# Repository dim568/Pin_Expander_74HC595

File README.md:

# Pin_Expander_74HC595
SPI Expander Board On 74HC595

KiCAD 4.0.4
PCB Design 03.05.17

PCB Have SilkScreen numeration error
- 23 -> 16
- 22 -> 17
- 21 -> 18
- 20 -> 19
- 19 -> 20
- 18 -> 21
- 17 -> 22
- 16 -> 23
- 15 -> 08
- 14 -> 09
- 13 -> 10
- 12 -> 11
- 11 -> 12
- 10 -> 13
- 09 -> 14
- 08 -> 15
- 07 -> 00
- 06 -> 01
- 05 -> 02
- 04 -> 03
- 03 -> 04
- 02 -> 05
- 01 -> 06
- 00 -> 07

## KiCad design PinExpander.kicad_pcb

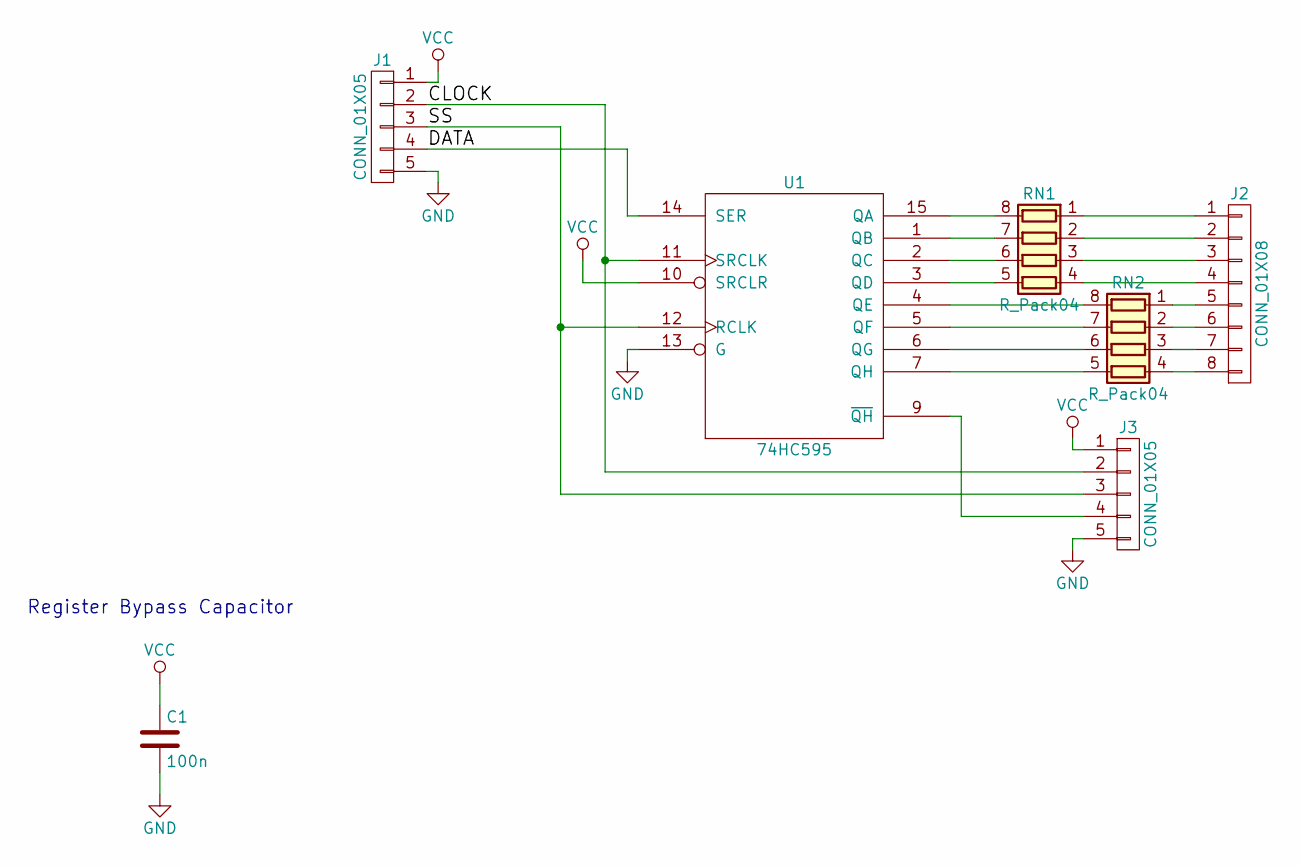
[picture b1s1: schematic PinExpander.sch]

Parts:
C1: 100n; C_1206_HandSoldering
J1, J3: CONN_01X05; Pin_Header_Straight_1x05_Pitch2.54mm
J2: CONN_01X08; Pin_Header_Straight_1x08_Pitch2.54mm
RN1, RN2: R_Pack04; R_Array_Convex_4x0603
U1: 74HC595; SOIC-16_3.9x9.9mm_Pitch1.27mm

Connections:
/CLOCK: J1.2, J3.2, U1.11 (SRCLK)
/DATA: J1.4, U1.14 (SER)
/SS: J1.3, J3.3, U1.12 (RCLK)
GND: C1.2, J1.5, J3.5, U1.8 (GND), U1.13 (G)
unnamed: J2.1, RN1.1 (R1.1)
unnamed: J2.2, RN1.2 (R2.1)
unnamed: J2.3, RN1.3 (R3.1)
unnamed: J2.4, RN1.4 (R4.1)
unnamed: J2.5, RN2.1 (R1.1)
unnamed: J2.6, RN2.2 (R2.1)
unnamed: J2.7, RN2.3 (R3.1)
unnamed: J2.8, RN2.4 (R4.1)
unnamed: J3.4, U1.9 (~QH)
unnamed: RN1.5 (R4.2), U1.3 (QD)
unnamed: RN1.6 (R3.2), U1.2 (QC)
unnamed: RN1.7 (R2.2), U1.1 (QB)
unnamed: RN1.8 (R1.2), U1.15 (QA)
unnamed: RN2.5 (R4.2), U1.7 (QH)
unnamed: RN2.6 (R3.2), U1.6 (QG)
unnamed: RN2.7 (R2.2), U1.5 (QF)
unnamed: RN2.8 (R1.2), U1.4 (QE)
VCC: C1.1, J1.1, J3.1, U1.10 (SRCLR), U1.16 (VCC)

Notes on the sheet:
Register Bypass Capacitor

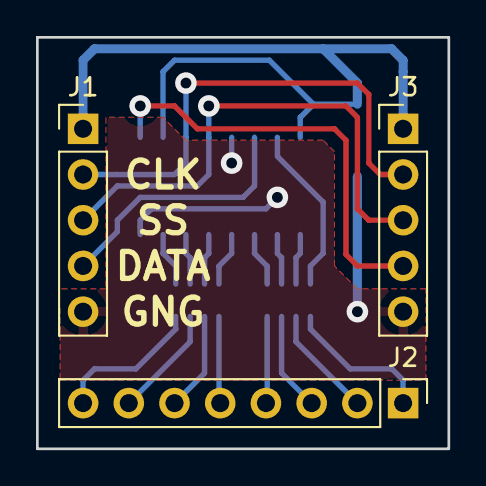
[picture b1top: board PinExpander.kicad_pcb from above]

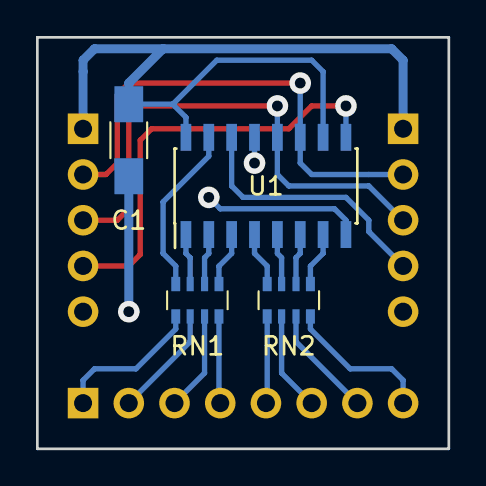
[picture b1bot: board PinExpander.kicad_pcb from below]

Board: 2 copper layers, 22.9 x 22.9 mm, 7 parts (4 on the bottom side), 22 nets.

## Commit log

2017-05-30 Init
2017-06-01 New stackable version
